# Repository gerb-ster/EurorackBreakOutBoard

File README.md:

# Eurorack BreakOut Board

A simple breakout board to help development of Eurorack modules. Clips on your breadboard and
provides a power connector, power indicator lights and some I/O terminals.

## Features

- 4 IO ports
- Power indicator led for both +12v and -12v rails
- Selectable ground rails

## Sponsoring

This project was kindly sponsored by [PCBWay](https://www.pcbway.com/?from=gerbster). They offer a fast and very affordable PCB manufacturing service. I find that their ordering process is very intuitive and the boards are of exceptional quality, so I highly recommend them.

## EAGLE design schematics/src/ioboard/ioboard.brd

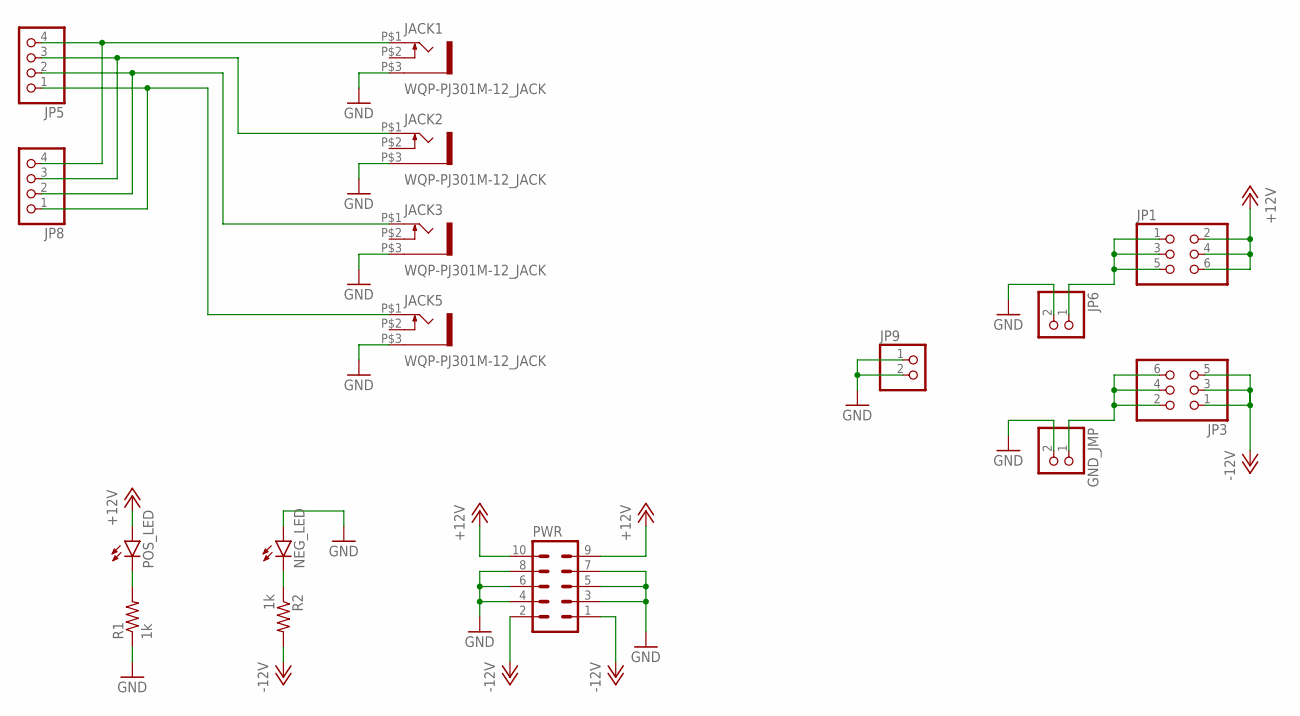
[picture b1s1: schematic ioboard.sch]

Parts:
GND_JMP: PINHD-1X2; 1X02
JACK1, JACK2, JACK3, JACK5: WQP-PJ301M-12_JACK
JP1, JP3: PINHD-2X3; 2X03
JP5, JP8: PINHD-1X4; 1X04
JP6, JP9: PINHD-1X2; 1X02
NEG_LED: LED3MM
POS_LED: LED3MM
PWR: ML10
R1, R2: 1k; 0207/7

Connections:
+12V: JP1.2, JP1.4, JP1.6, POS_LED.A, PWR.9, PWR.10
-12V: JP3.1, JP3.3, JP3.5, PWR.1, PWR.2, R2.2
GND: GND_JMP.2, JACK1.P$3 (1), JACK2.P$3 (1), JACK3.P$3 (1), JACK5.P$3 (1), JP6.2, JP9.1, JP9.2, NEG_LED.A, PWR.3, PWR.4, PWR.5, PWR.6, PWR.7, PWR.8, R1.1
unnamed: POS_LED.K (C), R1.2
unnamed: NEG_LED.K (C), R2.1
unnamed: JACK1.P$1 (2), JP5.4, JP8.4
unnamed: JACK3.P$1 (2), JP5.2, JP8.2
unnamed: JP1.1, JP1.3, JP1.5, JP6.1
unnamed: JACK5.P$1 (2), JP5.1, JP8.1
unnamed: GND_JMP.1, JP3.2, JP3.4, JP3.6
unnamed: JACK2.P$1 (2), JP5.3, JP8.3

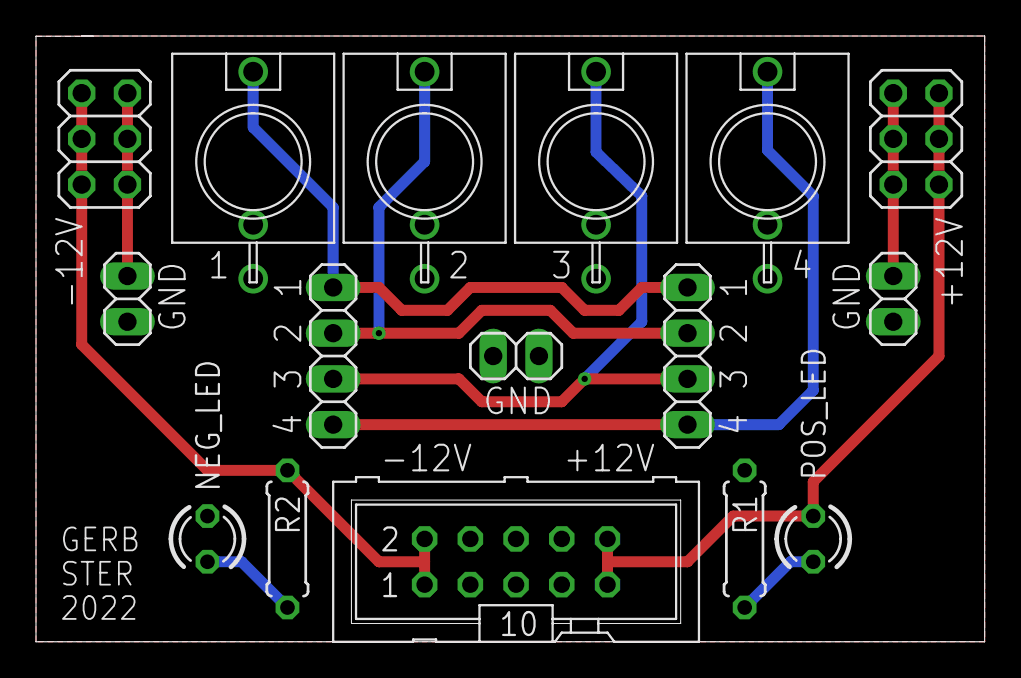
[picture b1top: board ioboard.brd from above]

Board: 2 copper layers, 52.7 x 33.7 mm, 16 parts (0 on the bottom side), 11 nets.

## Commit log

2022-04-22 Fixed schematics & descriptions
2022-04-22 fixed small issues
2022-04-22 fixed headers
2022-05-17 Updated Firmware
2022-05-18 Updated Faceplates
2022-05-18 Fixed issues
2022-05-21 Fixed schematics
2022-05-28 General updates
2022-06-13 Faceplates & Bugfixes
